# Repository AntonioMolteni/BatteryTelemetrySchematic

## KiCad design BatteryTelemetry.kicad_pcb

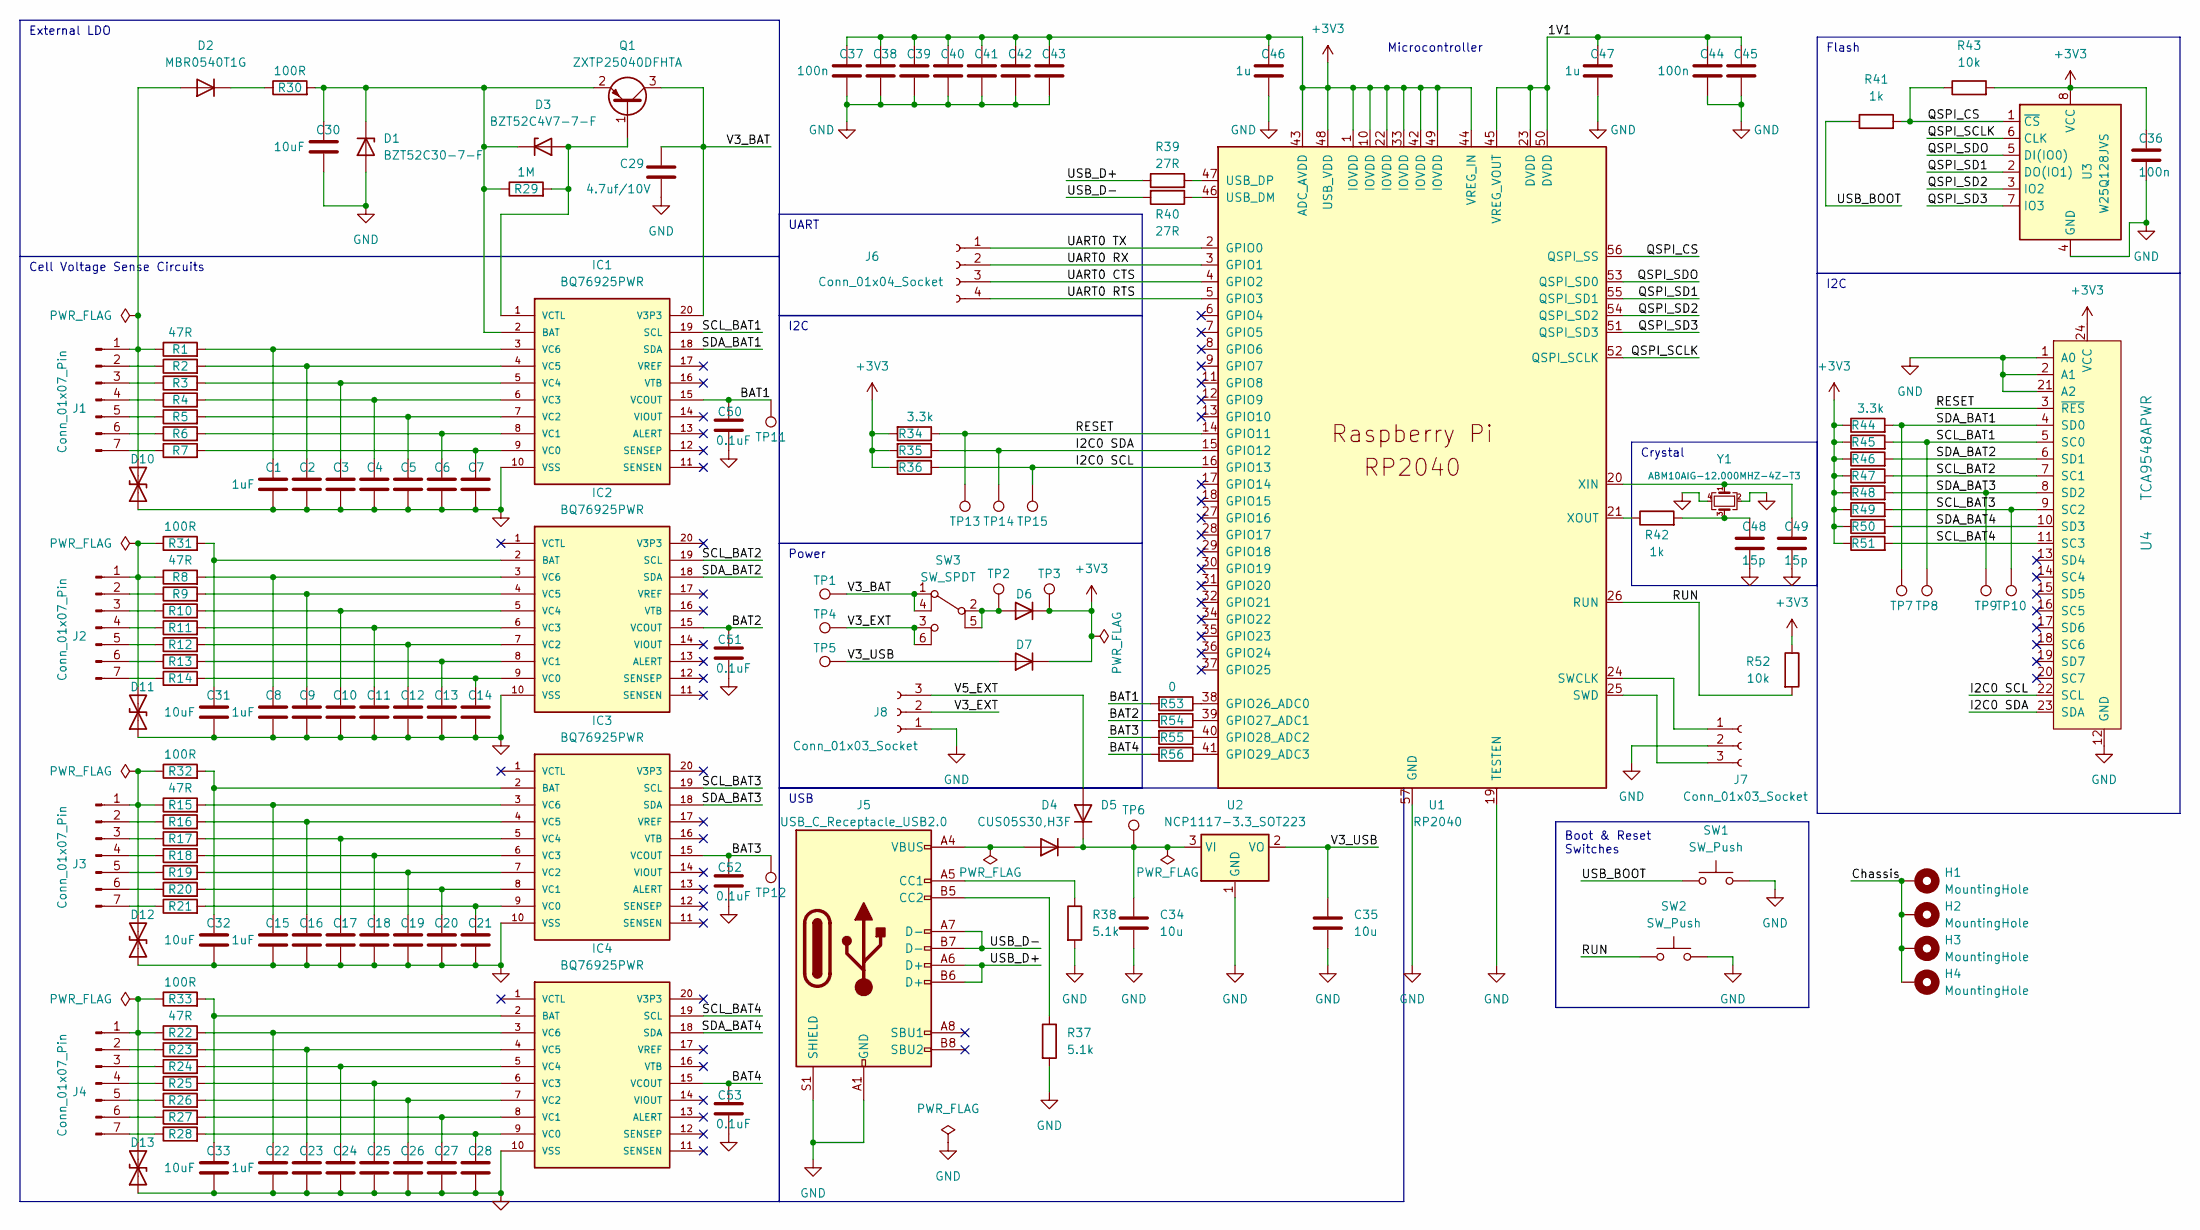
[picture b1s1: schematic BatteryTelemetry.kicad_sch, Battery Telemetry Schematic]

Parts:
C1, C2, C3, C4, C5, C6, C7, C8, C9, C10, C11, C12, C13, C14, C15, C16, C17, C18, C19, C20, C21, C22, C23, C24, C25, C26, C27, C28: 1uF; C_0805_2012Metric_Pad1.18x1.45mm_HandSolder
C29: 4.7uf/10V; C_0805_2012Metric_Pad1.18x1.45mm_HandSolder
C30, C31, C32, C33: 10uF; C_0805_2012Metric_Pad1.18x1.45mm_HandSolder
C34, C35: 10u; C_0805_2012Metric_Pad1.18x1.45mm_HandSolder
C36, C37, C38, C39, C40, C41, C42, C43, C44, C45: 100n; C_0805_2012Metric_Pad1.18x1.45mm_HandSolder
C46, C47: 1u; C_0805_2012Metric_Pad1.18x1.45mm_HandSolder
C48, C49: 15p; C_0805_2012Metric_Pad1.18x1.45mm_HandSolder
C50, C51, C52, C53: 0.1uF; C_0805_2012Metric_Pad1.18x1.45mm_HandSolder
D1: BZT52C30-7-F; D_SOD-123
D2: MBR0540T1G; D_SOD-123
D3: BZT52C4V7-7-F; D_SOD-123
D4, D5, D6, D7: CUS05S30,H3F; D_SOD-323_HandSoldering
D10, D11, D12, D13: SMBJ28CA; D_SMB_Handsoldering
H1, H2, H3, H4: MountingHole; MountingHole_3.2mm_M3_DIN965_Pad
IC1, IC2, IC3, IC4: BQ76925PWR; SOP65P640X120-20N; MOUSER_PART_NUMBER 595-BQ76925PWR; DigiKey_Part_Number 296-29341-2-ND
J1, J2, J3, J4: Conn_01x07_Pin; JST_XH_S7B-XH-A-1_1x07_P2.50mm_Horizontal
J5: USB_C_Receptacle_USB2.0; USB_C_Receptacle_GCT_USB4085
J6: Conn_01x04_Socket; PinSocket_1x04_P2.54mm_Vertical
J7, J8: Conn_01x03_Socket; PinSocket_1x03_P2.54mm_Vertical
Q1: ZXTP25040DFHTA; SOT-23-3
R1, R2, R3, R4, R5, R6, R7, R8, R9, R10, R11, R12, R13, R14, R15, R16, R17, R18, R19, R20, R21, R22, R23, R24, R25, R26, R27, R28: 47R; R_0805_2012Metric_Pad1.20x1.40mm_HandSolder
R29: 1M; R_0805_2012Metric_Pad1.20x1.40mm_HandSolder
R30, R31, R32, R33: 100R; R_0805_2012Metric_Pad1.20x1.40mm_HandSolder
R34, R35, R36, R44, R45, R46, R47, R48, R49, R50, R51: 3.3k; R_0805_2012Metric_Pad1.20x1.40mm_HandSolder
R37, R38: 5.1k; R_0805_2012Metric_Pad1.20x1.40mm_HandSolder
R39, R40: 27R; R_0805_2012Metric_Pad1.20x1.40mm_HandSolder
R41, R42: 1k; R_0805_2012Metric_Pad1.20x1.40mm_HandSolder
R43, R52: 10k; R_0805_2012Metric_Pad1.20x1.40mm_HandSolder
R53, R54, R55, R56: 0; R_0805_2012Metric_Pad1.20x1.40mm_HandSolder
SW1, SW2: SW_Push; SW_PUSH_1P1T_6x3.5mm_H4.3_APEM_MJTP1243
SW3: SW_SPDT; SW_E-Switch_EG1271_SPDT
TP1, TP2, TP3, TP4, TP5, TP6, TP7, TP8, TP9, TP10, TP11, TP12, TP13, TP14, TP15: TestPoint; TestPoint_THTPad_D1.5mm_Drill0.7mm
U1: RP2040; RP2040-QFN-56
U2: NCP1117-3.3_SOT223; SOT-223-3_TabPin2
U3: W25Q128JVS; SOIC-8_5.23x5.23mm_P1.27mm
U4: TCA9548APWR; TSSOP-24_4.4x7.8mm_P0.65mm; MPN TCA9548APWR; Digi-Key_PN 296-34905-1-ND
Y1: ABM10AIG-12.000MHZ-4Z-T3; Crystal_SMD_Abracon_ABM10-4Pin_2.5x2.0mm

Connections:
+3V3: C36.1, C37.1, C38.1, C39.1, C40.1, C41.1, C42.1, C43.1, C46.1, D6.1 (K), D7.1 (K), R34.2, R35.2, R36.2, R43.2, R44.1, R45.1, R46.1, R47.1, R48.1, R49.1, R50.1, R51.1, R52.1, TP3.1, U1.1 (IOVDD), U1.10 (IOVDD), U1.22 (IOVDD), U1.33 (IOVDD), U1.42 (IOVDD), U1.43 (ADC_AVDD), U1.44 (VREG_IN), U1.48 (USB_VDD), U1.49 (IOVDD), U3.8 (VCC), U4.24 (VCC)
/1V1: C44.1, C45.1, C47.1, U1.23 (DVDD), U1.45 (VREG_VOUT), U1.50 (DVDD)
/BAT1: C50.1, IC1.15 (VCOUT), R53.2, TP11.1
/BAT2: C51.1, IC2.15 (VCOUT), R54.2
/BAT3: C52.1, IC3.15 (VCOUT), R55.2, TP12.1
/BAT4: C53.1, IC4.15 (VCOUT), R56.2
/Chassis: H1.1, H2.1, H3.1, H4.1
/I2C0 SCL: R36.1, TP15.1, U1.16 (GPIO13), U4.22 (SCL)
/I2C0 SDA: R35.1, TP14.1, U1.15 (GPIO12), U4.23 (SDA)
/QSPI_CS: R41.2, R43.1, U1.56 (QSPI_SS), U3.1 (~CS)
/QSPI_SCLK: U1.52 (QSPI_SCLK), U3.6 (CLK)
/QSPI_SD1: U1.55 (QSPI_SD1), U3.2 (DO(IO1))
/QSPI_SD2: U1.54 (QSPI_SD2), U3.3 (IO2)
/QSPI_SD3: U1.51 (QSPI_SD3), U3.7 (IO3)
/QSPI_SDO: U1.53 (QSPI_SD0), U3.5 (DI(IO0))
/RESET: R34.1, TP13.1, U1.14 (GPIO11), U4.3 (~RES)
/RUN: R52.2, SW2.1, U1.26 (RUN)
/SCL_BAT1: IC1.19 (SCL), R45.2, TP8.1, U4.5 (SC0)
/SCL_BAT2: IC2.19 (SCL), R47.2, U4.7 (SC1)
/SCL_BAT3: IC3.19 (SCL), R49.2, TP10.1, U4.9 (SC2)
/SCL_BAT4: IC4.19 (SCL), R51.2, U4.11 (SC3)
/SDA_BAT1: IC1.18 (SDA), R44.2, TP7.1, U4.4 (SD0)
/SDA_BAT2: IC2.18 (SDA), R46.2, U4.6 (SD1)
/SDA_BAT3: IC3.18 (SDA), R48.2, TP9.1, U4.8 (SD2)
/SDA_BAT4: IC4.18 (SDA), R50.2, U4.10 (SD3)
/UART0 CTS: J6.3, U1.4 (GPIO2)
/UART0 RTS: J6.4, U1.5 (GPIO3)
/UART0 RX: J6.2, U1.3 (GPIO1)
/UART0 TX: J6.1, U1.2 (GPIO0)
/USB_BOOT: R41.1, SW1.1
/USB_D+: J5.A6 (D+), J5.B6 (D+), R39.1
/USB_D-: J5.A7 (D-), J5.B7 (D-), R40.2
/V3_BAT: C29.1, IC1.20 (V3P3), Q1.3 (C), SW3.1 (A), SW3.4, TP1.1
/V3_EXT: J8.2, SW3.3 (C), SW3.6, TP4.1
/V3_USB: C35.1, D7.2 (A), TP5.1, U2.2 (VO)
/V5_EXT: D5.2 (A), J8.3
GND: C1.2, C2.2, C3.2, C4.2, C5.2, C6.2, C7.2, C8.2, C9.2, C10.2, C11.2, C12.2, C13.2, C14.2, C15.2, C16.2, C17.2, C18.2, C19.2, C20.2, C21.2, C22.2, C23.2, C24.2, C25.2, C26.2, C27.2, C28.2, C29.2, C30.2, C31.2, C32.2, C33.2, C34.2, C35.2, C36.2, C37.2, C38.2, C39.2, C40.2, C41.2, C42.2, C43.2, C44.2, C45.2, C46.2, C47.2, C48.2, C49.2, C50.2, C51.2, C52.2, C53.2, D1.2 (A), D10.1 (A1), D11.1 (A1), D12.1 (A1), D13.1 (A1), IC1.10 (VSS), IC2.10 (VSS), IC3.10 (VSS), IC4.10 (VSS), J5.A1 (GND), J5.A12 (GND), J5.B1 (GND), J5.B12 (GND), J5.S1 (SHIELD), J7.2, J8.1, R37.2, R38.2, SW1.2, SW2.2, U1.19 (TESTEN), U1.57 (GND), U2.1 (GND), U3.4 (GND), U4.1 (A0), U4.2 (A1), U4.12 (GND), U4.21 (A2), Y1.2, Y1.4
unnamed: C48.1, R42.2, Y1.3
unnamed: C30.1, D1.1 (K), D3.1 (K), IC1.2 (BAT), Q1.2 (E), R29.1, R30.2
unnamed: D2.1 (K), R30.1
unnamed: D3.2 (A), IC1.1 (VCTL), Q1.1 (B), R29.2
unnamed: D4.2 (A), J5.A4 (VBUS), J5.A9 (VBUS), J5.B4 (VBUS), J5.B9 (VBUS)
unnamed: C34.1, D4.1 (K), D5.1 (K), TP6.1, U2.3 (VI)
unnamed: D6.2 (A), SW3.2 (B), SW3.5, TP2.1
unnamed: D2.2 (A), D10.2 (A2), J1.1, R1.1
unnamed: D11.2 (A2), J2.1, R8.1, R31.1
unnamed: D12.2 (A2), J3.1, R15.1, R32.1
unnamed: D13.2 (A2), J4.1, R22.1, R33.1
unnamed: C7.1, IC1.9 (VC0), R7.2
unnamed: C6.1, IC1.8 (VC1), R6.2
unnamed: C5.1, IC1.7 (VC2), R5.2
unnamed: C4.1, IC1.6 (VC3), R4.2
unnamed: C3.1, IC1.5 (VC4), R3.2
unnamed: C2.1, IC1.4 (VC5), R2.2
unnamed: C1.1, IC1.3 (VC6), R1.2
unnamed: C31.1, IC2.2 (BAT), R31.2
unnamed: C14.1, IC2.9 (VC0), R14.2
unnamed: C13.1, IC2.8 (VC1), R13.2
unnamed: C12.1, IC2.7 (VC2), R12.2
unnamed: C11.1, IC2.6 (VC3), R11.2
unnamed: C10.1, IC2.5 (VC4), R10.2
unnamed: C9.1, IC2.4 (VC5), R9.2
unnamed: C8.1, IC2.3 (VC6), R8.2
unnamed: C32.1, IC3.2 (BAT), R32.2
unnamed: C21.1, IC3.9 (VC0), R21.2
unnamed: C20.1, IC3.8 (VC1), R20.2
unnamed: C19.1, IC3.7 (VC2), R19.2
unnamed: C18.1, IC3.6 (VC3), R18.2
unnamed: C17.1, IC3.5 (VC4), R17.2
unnamed: C16.1, IC3.4 (VC5), R16.2
unnamed: C15.1, IC3.3 (VC6), R15.2
unnamed: C33.1, IC4.2 (BAT), R33.2
unnamed: C28.1, IC4.9 (VC0), R28.2
unnamed: C27.1, IC4.8 (VC1), R27.2
unnamed: C26.1, IC4.7 (VC2), R26.2
unnamed: C25.1, IC4.6 (VC3), R25.2
unnamed: C24.1, IC4.5 (VC4), R24.2
unnamed: C23.1, IC4.4 (VC5), R23.2
unnamed: C22.1, IC4.3 (VC6), R22.2
unnamed: J1.2, R2.1
unnamed: J1.3, R3.1
unnamed: J1.4, R4.1
unnamed: J1.5, R5.1
unnamed: J1.6, R6.1
unnamed: J1.7, R7.1
unnamed: J2.2, R9.1
unnamed: J2.3, R10.1
unnamed: J2.4, R11.1
unnamed: J2.5, R12.1
unnamed: J2.6, R13.1
unnamed: J2.7, R14.1
unnamed: J3.2, R16.1
unnamed: J3.3, R17.1
unnamed: J3.4, R18.1
unnamed: J3.5, R19.1
unnamed: J3.6, R20.1
unnamed: J3.7, R21.1
unnamed: J4.2, R23.1
unnamed: J4.3, R24.1
unnamed: J4.4, R25.1
unnamed: J4.5, R26.1
unnamed: J4.6, R27.1
unnamed: J4.7, R28.1
unnamed: J5.A5 (CC1), R38.1
unnamed: J5.B5 (CC2), R37.1
unnamed: J7.1, U1.24 (SWCLK)
unnamed: J7.3, U1.25 (SWD)
unnamed: R53.1, U1.38 (GPIO26_ADC0)
unnamed: R54.1, U1.39 (GPIO27_ADC1)
unnamed: R55.1, U1.40 (GPIO28_ADC2)
unnamed: R56.1, U1.41 (GPIO29_ADC3)
unnamed: R40.1, U1.46 (USB_DM)
unnamed: R39.2, U1.47 (USB_DP)
unnamed: C49.1, U1.20 (XIN), Y1.1
unnamed: R42.1, U1.21 (XOUT)

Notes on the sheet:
UART
Power
Boot & Reset Switches
Cell Voltage Sense Circuits
I2C
Microcontroller
Flash
External LDO
Crystal
USB
I2C

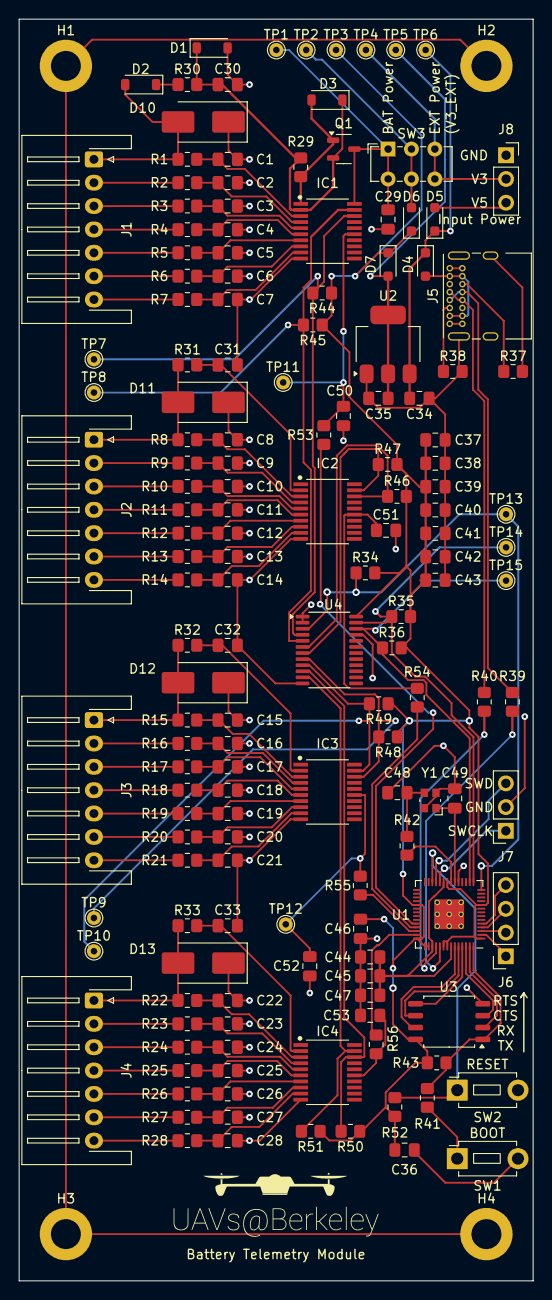
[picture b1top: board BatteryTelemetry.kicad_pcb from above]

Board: 2 copper layers, 55.0 x 135.0 mm, 160 parts (0 on the bottom side), 115 nets.

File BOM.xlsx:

Instructions
Fill in the cells with the YELLOW highlight. Do not edit red cells. Fill out th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 |  |  |  |  |  |  |  |  |  |  | Total Price for Project
 |  |  |  |  |  |  |  |  |  |  | 57.89
Qty (for 1 board) | Manufacturer Part # | Digi-key Part#/SKU | Mouser Part#/SKU | Price/unit ($) | Purchase URL | Reference Designator | Description (include component value if applicable) | Datasheet Link | Multiple | Total Qty | Total Price/part ($)
4.0 | BQ76925PWR | 296-29341-1-ND |  | 2.15 | https://www.digikey.com/en/products/detail/texas-instruments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 |  | IC1-IC4, BMS | https://www.ti.com/lit/ds/symlink/bq76925.pdf |  | 5.0 | 10.75
28.0 | CR0805-JW-470ELF | 118-CR0805-JW-470ELFCT-ND |  | 0.1 | https://www.digikey.com/en/products/detail/bourns-inc/CR0805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 |  | R1-R28 47R | https://www.bourns.com/docs/product-datasheets/cr.pdf?sfvrsn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 |  | 50.0 | 5
28.0 | CL21B105KAFNNNE | 1276-1066-1-ND |  | 0.1 | https://www.digikey.com/en/products/detail/samsung-electro-m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 |  | C1-C28 1uF | https://mm.digikey.com/Volume0/opasdata/d220001/medias/docus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 |  | 50.0 | 5
4.0 | S7B-XH-A | 455-S7B-XH-A-ND |  | 0.49 | https://www.digikey.com/en/products/detail/jst-sales-america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 |  | J1-J4 6S Connectors | https://www.jst-mfg.com/product/pdf/eng/eXH.pdf |  | 5.0 | 2.45
4.0 | SMBJ28CA | SMBJ28CALFCT-ND |  | 0.47 | https://www.digikey.com/en/products/detail/littelfuse-inc/SM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 |  | D10-D13 TVS Diode | https://www.littelfuse.com/media?resourcetype=datasheets&ite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 |  | 6.0 | 2.82
4.0 | CR0805-JW-101ELF | CR0805-JW-101ELFCT-ND |  | 0.1 | https://www.digikey.com/en/products/detail/bourns-inc/CR0805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 |  | R30-33, 100R, LDO | https://www.bourns.com/docs/product-datasheets/cr.pdf?sfvrsn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 |  | 10.0 | 1
4.0 | GRM21BR61H106KE43K | 490-GRM21BR61H106KE43KCT-ND |  | 0.34 | https://www.digikey.com/en/products/detail/murata-electronic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 |  | C30-C33 10uF/50V | https://search.murata.co.jp/Ceramy/image/img/A01X/G101/ENG/G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 |  | 4 | 1.36
4.0 | CR0805-J-000ELF | CR0805-J/-000ELFCT-ND |  | 0.1 | https://www.digikey.com/en/products/detail/bourns-inc/CR0805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 |  | R53-56 0R, VCout to MCU | https://www.bourns.com/docs/product-datasheets/cr.pdf?sfvrsn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 |  | 10.0 | 1
4.0 | CL21B104KBFNNNE | 1276-1180-1-ND |  | 0.1 | https://www.digikey.com/en/products/detail/samsung-electro-m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 |  | C50-53 0.1uF, VCout to MCU | http://www.samsungsem.com/kr/support/product-search/mlcc/CL2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 |  | 10.0 | 1
1.0 | CR0805-JW-105ELF | CR0805-JW-105ELFCT-ND |  | 0.1 | https://www.digikey.com/en/products/detail/bourns-inc/CR0805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 |  | R29, 1MOhms, LDO | https://www.bourns.com/docs/product-datasheets/cr.pdf?sfvrsn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 |  | 10.0 | 1
1.0 | CL21A475KPFNNNG | 1276-6464-1-ND |  | 0.1 | https://www.digikey.com/en/products/detail/samsung-electro-m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 |  | C29, 4.7uF/10V | https://mm.digikey.com/Volume0/opasdata/d220001/medias/docus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 |  | 3.0 | 0.3
1.0 | BZT52C30-7-F | BZT52C30-FDICT-ND |  | 0.21 | https://www.digikey.com/en/products/detail/diodes-incorporat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 |  | D1, Diode, LDO | https://www.diodes.com/assets/Datasheets/ds18004.pdf |  | 2.0 | 0.42
1.0 | MBR0540T1G | MBR0540T1GOSCT-ND |  | 0.47 | https://www.digikey.com/en/products/detail/onsemi/MBR0540T1G/918576 |  | D2, Diode, LDO | https://www.onsemi.com/pdf/datasheet/mbr0540t1-d.pdf |  | 2.0 | 0.94
1.0 | BZT52C4V7-7-F | BZT52C4V7-FDICT-ND |  | 0.21 | https://www.digikey.com/en/products/detail/diodes-incorporat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 |  | D3, Diode, LDO | https://www.diodes.com/assets/Datasheets/ds18004.pdf |  | 2.0 | 0.42
1.0 | ZXTP25040DFHTA | ZXTP25040DFHCT-ND |  | 0.57 | https://www.digikey.com/en/products/detail/diodes-incorporat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 |  | Q1, BJT, LDO | https://www.diodes.com/assets/Datasheets/ZXTP25040DFH.pdf |  | 2.0 | 1.14
1.0 | SC0914(7) | 2648-SC0914(7)CT-ND |  | 0.8 | https://www.digikey.com/en/products/detail/raspberry-pi/SC09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 |  | U1 Controller rp2040 | https://datasheets.raspberrypi.com/rp2040/rp2040-datasheet.pdf |  | 2.0 | 1.6
1.0 | USB4085-GF-A | 2073-USB4085-GF-ACT-ND |  | 0.94 | https://www.digikey.com/en/products/detail/gct/USB4085-GF-A/9859662 |  | J5 Type C USB 2.0 receptacle | https://gct.co/files/drawings/usb4085.pdf |  | 1.0 | 0.94
2.0 | RC0805FR-0710KL | 311-10.0KCRCT-ND |  | 0.1 | https://www.digikey.com/en/products/detail/yageo/RC0805FR-07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 |  | R43, R52 10k | https://www.yageo.com/upload/media/product/products/datashee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 |  | 2 | 0.2
2.0 | RC0805JR-075K1L | 311-5.1KARCT-ND |  | 0.1 | https://www.digikey.com/en/products/detail/yageo/RC0805JR-07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 |  | R37-R38 5.1k | https://www.yageo.com/upload/media/product/products/datashee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 |  | 2 | 0.2
2.0 | CL21A106KOQNNNE | 1276-1096-1-ND |  | 0.1 | https://www.digikey.com/en/products/detail/samsung-electro-m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 |  | C34-C35 10u | https://mm.digikey.com/Volume0/opasdata/d220001/medias/docus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 |  | 5.0 | 0.5
1.0 | NCP1117LPST33T3G | NCP1117LPST33T3GOSCT-ND |  | 0.47 | https://www.digikey.com/en/products/detail/onsemi/NCP1117LPS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 |  | U2 NCP1117 -3.3V_SOT223 | https://www.onsemi.com/pdf/datasheet/ncp1117lp-d.pdf |  | 0.0 | 0
1.0 | RC0805JR-0727RL | 311-27ARCT-ND |  | 0.1 | https://www.digikey.com/en/products/detail/yageo/RC0805JR-07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 |  | R39-R40 27R | https://www.yageo.com/upload/media/product/products/datashee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 |  | 10.0 | 1
1.0 | RC0805FR-071KL | 311-1.00KCRCT-ND |  | 0.1 | https://www.digikey.com/en/products/detail/yageo/RC0805FR-07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 |  | R41-R42 1k | https://www.yageo.com/upload/media/product/products/datashee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 |  | 10.0 | 1
10.0 | CC0805KRX7R9BB104 | 311-1140-1-ND |  | 0.1 | https://www.digikey.com/en/products/detail/yageo/CC0805KRX7R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 |  | C36-C45 100n (0.1u) | https://www.yageo.com/upload/media/product/app/datasheet/mlc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 |  | 20.0 | 2
2.0 | CL21B105KAFNNNE | 1276-1066-1-ND |  | 0.1 | https://www.digikey.com/en/products/detail/samsung-electro-m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 |  | C46-C47 1u | https://mm.digikey.com/Volume0/opasdata/d220001/medias/docus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 |  | 0.0 | 0
2.0 | MJTP1243 | 679-2452-ND |  | 0.36 | https://www.digikey.com/en/products/detail/apem-inc/MJTP1243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 |  | SW1-SW2 | https://mm.digikey.com/Volume0/opasdata/d220001/medias/docus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 |  | 4.0 | 1.44
1.0 | PPPC041LFBN-RC | S7037-ND |  | 0.47 | https://www.digikey.com/en/products/detail/sullins-connector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 |  | J6 1 by 4 female header | https://mm.digikey.com/Volume0/opasdata/d220001/medias/docus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 |  | 2.0 | 0.94
1.0 | TCA9548APWR | 296-34905-1-ND |  | 1.6 | https://www.digikey.com/en/products/detail/texas-instruments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 |  | U4 I2C Multiplexer | https://www.ti.com/general/docs/suppproductinfo.tsp?distId=1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 |  | 2.0
11.0 | RC0805FR-073K3L | 311-3.30KCRCT-ND |  | 0.1 | https://www.digikey.com/en/products/detail/yageo/RC0805FR-07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 |  | R34-R36,R44-R51 3.3kOhm | https://www.yageo.com/upload/media/product/products/datashee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 |  | 20.0 | 2
4.0 | CUS05S30,H3F | CUS05S30H3FCT-ND |  | 0.31 | https://www.digikey.com/en/products/detail/toshiba-semicondu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 |  | D4-D7 | https://toshiba.semicon-storage.com/info/CUS05S30_datasheet_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 |  | 6.0 | 1.86
2.0 | PPPC031LFBN-RC | S7036-ND |  | 0.38 | https://www.digikey.com/en/products/detail/sullins-connector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 |  | J7-J8 1 by 3 female header | https://mm.digikey.com/Volume0/opasdata/d220001/medias/docus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 |  | 4.0 | 1.52
1.0 | EG1271 | EG1918-ND |  | 0.85 | https://www.digikey.com/en/products/detail/e-switch/EG1271/251335 |  | SW3 SPDT | https://sten-eswitch-13110800-production.s3.amazonaws.com/sy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 |  | 2.0 | 1.7
1.0 | W25Q128JVSIQ TR | W25Q128JVSIQCT-ND |  | 1.78 | https://www.digikey.com/en/products/detail/winbond-electroni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 |  | U4 W25Q128JVS | https://www.winbond.com/resource-files/w25q128jv%20revf%2003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 |  | 2.0 | 3.56
1.0 | ABM10AIG-12.000MHZ-4Z-T3 | 535-13360-1-ND |  | 0.61 | https://www.digikey.com/en/products/detail/abracon-llc/ABM10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 |  | Y1 Crystal (AMB8-282-T3 Not available) | https://abracon.com/AIGcrystals/ABM10AIG.pdf |  | 3.0 | 1.83
2.0 | CC0805JRNPO9BN150 | 311-1101-1-ND |  | 0.1 | https://www.digikey.com/en/products/detail/yageo/CC0805JRNPO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 |  | C48-C49 15p | https://www.yageo.com/upload/media/product/productsearch/dat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 |  | 10.0 | 1

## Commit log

2024-03-25 schematic complete
2024-04-02 footprint v1 (unfinished)
2024-04-02 footprint v2 (nothing new)
2024-04-03 button fixed
2024-04-06 Layout Complete
2024-04-09 finished layout
2024-04-11 Updated Layout
2024-04-21 RC circuit for VCout
2024-04-22 RC for Vcout Layout Updated
2024-04-24 Layout updated
2024-04-24 gerbers updated
2024-05-05 Logo added
